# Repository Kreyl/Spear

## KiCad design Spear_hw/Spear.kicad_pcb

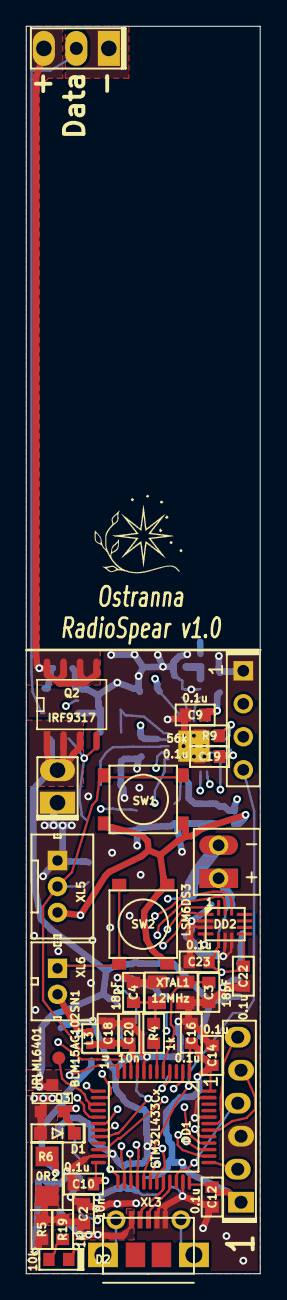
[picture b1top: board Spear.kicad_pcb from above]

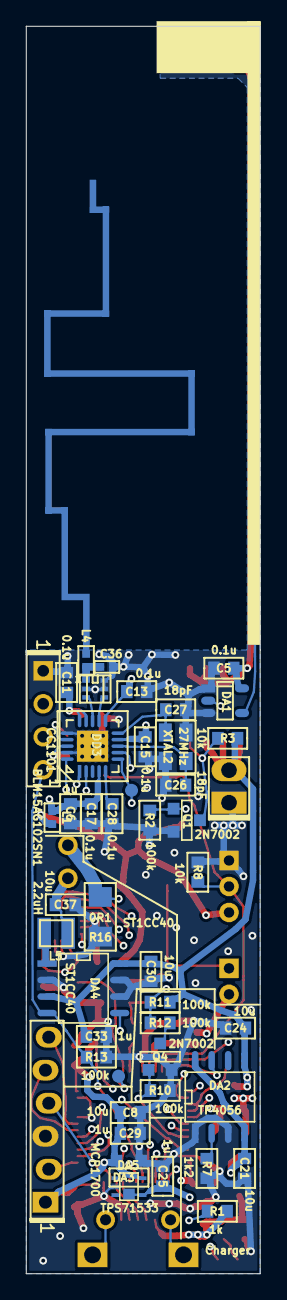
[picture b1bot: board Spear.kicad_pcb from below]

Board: 4 copper layers, 18.0 x 96.0 mm, 82 parts (44 on the bottom side), 58 nets.

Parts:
ANT1: ANT_PCB_MONO; ANT_868_Spear_inverted
BLN1: BALUN868JOHANSON; BALUN_JOHANSON868
C2, C20: 10n; CAP_0603_Silks
C3, C4, C26, C27: 18pF; CAP_0603_Silks
C5, C9, C10, C11, C12, C13, C14, C15, C16, C17, C19, C22, C23, C28: 0.1u; CAP_0603_Silks
C6, C18, C25, C29, C33: 1u; CAP_0603_Silks
C8, C21, C24, C30, C37: 10u; CAP_0603_Silks
C36: *; CAP_0402
D1: NSR0320; SOD323
D2: LED; LED_0603
DA1: MC74VHC1; SOT23-5
DA2: TP4056; SO8_150MIL
DA3: MCP1700; SOT23-3A
DA4: ST1CC40; SO8_150MIL
DA5: TPS71533; SOT323
DD1: STM32L433Cx; LQFP48
DD2: LSM6DS3; 14_3x2d5_p0d5
DD3: CC1101; QFN20
L1, L3: BLM15AG102SN1; IND_0402
L4: *; IND_0402
L5: 2.2uH; IND_SRN2512
Logo1: Logo; Ostranna_8x8
Q1, Q4: 2N7002; SOT23-3
Q2: IRF9317; SO8_150MIL
Q3: IRLML6401; SOT23-3
R1, R4, R19: 1k; RES_0603
R2, R10, R11, R12, R13: 100k; RES_0603
R3, R5, R8: 10k; RES_0603
R6: 0R2; RES_1206
R7: 1k2; RES_0603
R9: 56k; RES_0603
R16: 0R1; RES_1206
SW1, SW2: BUTTON; BTN_4x4_SMD
TP1, TP2, TP3: TESTPOINT; TESTPOINT_1MM
XL1: CONN_6; PLS-6_LOCK
XL2: CONN_2; SLD_2_2D5
XL3: USB_MICRO; USBmicro_MOLEX_1050170001
XL4: CONN_3; SLD_3_2D5
XL5: CONN_3; WB-03(MW-3M)
XL6: CONN_2; WB-02(MW-2M)
XL7: CONN_2; Oval3x1.5wHole0d9_x2
XL8: CONN_4; PLS-4
XTAL1: 12MHz; 03225C4
XTAL2: 27MHz; 03225C4

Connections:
+3v3: C8.2, C10.1, C12.1, C14.1, C16.1, C29.1, DA3.2, DA5.5, DD1.1, DD1.24, DD1.36, DD1.48, L1.2, L3.1, SW1.2, SW2.2, XL1.1, XL5.3, XL6.2
+BATT: C24.2, C30.1, C33.1, DA2.5, DA4.3, DA4.8, Q2.1, Q2.2, Q2.3, Q3.3, R3.1, R11.1, XL2.2
/5V_MID: C21.2, DA2.4, DA2.8, R6.2
/5V_USB: C2.2, D1.A, Q3.1, R1.2, R5.1, R6.1, R19.2, XL3.1
/ACC_CS: DD1.25, DD2.12
/ACC_INT1: DD1.2, DD2.4
/ACC_MISO: DD1.27, DD2.1
/ACC_MOSI: DD1.28, DD2.14
/ACC_PWR: C22.1, C23.1, DD1.22, DD2.5, DD2.8
/ACC_SCK: DD1.26, DD2.13
/ADC_BAT: DD1.19, R11.2, R12.1
/ADC_BAT_EN: DD1.20, Q4.1, R10.1
/BTN1: DD1.10, R8.1, SW1.1, XL5.2
/BTN2: DD1.11, SW2.1, XL6.1
/CC_CS: DD1.38, DD3.7
/CC_GDO0: DD1.18, DD3.6, TP2.1
/CC_MISO: DD1.40, DD3.2
/CC_MOSI: DD1.41, DD3.20
/CC_SCK: DD1.39, DD3.1
/DIN0: DA1.4, XL4.2
/IS_CHARGING: D2.C, DA2.7, DD1.12
/LED_CTRL1: DA4.4, DD1.29, R13.1, XL8.4
/LED_CTRL2: DD1.30, XL8.3
/LED_CTRL3: DD1.31, XL8.2
/MCU_VDDA: C18.1, C20.1, DD1.9, L3.2
/NPX1_CTRL: DA1.2, DD1.17
/NPX_PWR: C5.2, DA1.5, Q2.5, Q2.6, Q2.7, Q2.8, XL4.3
/NPX_PWR_EN: DD1.14, Q1.1, R2.2
/RF1: BLN1.4, DD3.12
/RF2: BLN1.3, DD3.13
/SWCLK: DD1.37, XL1.2
/SWDIO: DD1.34, XL1.4
/UART_RX: DD1.43, XL1.6
/UART_TX: DD1.42, XL1.5
/USB_DM: DD1.32, XL3.2
/USB_DP: DD1.33, XL3.3
GND: BLN1.2, BLN1.5, BLN1.6, C2.1, C3.2, C4.2, C5.1, C6.2, C8.1, C9.2, C10.2, C11.2, C12.2, C13.2, C14.2, C15.2, C16.2, C17.2, C18.2, C19.2, C20.2, C21.1, C22.2, C23.2, C24.1, C25.2, C26.2, C27.2, C28.1, C29.2, C30.2, C33.2, C36.2, C37.2, DA1.1, DA1.3, DA2.1, DA2.3, DA3.1, DA4.2, DA4.6, DA4.7, DA5.2, DD1.8, DD1.23, DD1.35, DD1.44, DD1.47, DD2.2, DD2.3, DD2.6, DD2.7, DD3.16, DD3.19, DD3.PAD, Q1.2, Q4.2, R2.1, R5.2, R7.2, R8.2, R9.2, R10.2, R13.2, R16.2, XL1.3, XL2.1, XL3.4, XL3.5, XL4.1, XL5.1, XL8.1, XTAL1.H, XTAL2.H
unnamed: ANT1.1, L4.2
unnamed: BLN1.1, C36.1, L4.1
unnamed: C3.1, DD1.5, XTAL1.1
unnamed: C4.1, R4.2, XTAL1.2
unnamed: C26.1, DD3.8, XTAL2.1
unnamed: C27.1, DD3.10, XTAL2.2
unnamed: C28.2, DD3.5
unnamed: C37.1, L5.1, XL7.1
unnamed: D2.A, R19.1
unnamed: DA2.2, R7.1
unnamed: DA4.1, L5.2
unnamed: DA4.5, R16.1, XL7.2
unnamed: DD1.4, TP1.1
unnamed: DD1.6, R4.1
unnamed: DD1.13, R1.1
unnamed: DD1.15, DD1.16, TP3.1
unnamed: DD3.17, R9.1
unnamed: Q1.3, Q2.4, R3.2
unnamed: Q4.3, R12.2
PwrUnst: C25.1, D1.C, DA3.3, DA5.4, Q3.2
VCC: C6.1, C9.1, C11.1, C13.1, C15.1, C17.1, C19.1, DD3.4, DD3.9, DD3.11, DD3.14, DD3.15, DD3.18, L1.1

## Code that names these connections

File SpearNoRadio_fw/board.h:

#pragma once

// ==== General ====
#define BOARD_NAME          "Spear01"
#define APP_NAME            "StaffWings"

#ifndef TRUE
#define TRUE    1
#endif

// ==== High-level peripery control ====
#define PILL_ENABLED        FALSE
#define BEEPER_ENABLED      FALSE
#define BUTTONS_ENABLED     TRUE

#define SIMPLESENSORS_ENABLED   BUTTONS_ENABLED

// MCU type as defined in the ST header.
#define STM32L151xB

// Freq of external crystal if any. Leave it here even if not used.
#define CRYSTAL_FREQ_HZ 12000000

// OS timer settings
#define STM32_ST_IRQ_PRIORITY   2
#define STM32_ST_USE_TIMER      2
#define SYS_TIM_CLK             (Clk.APB1FreqHz)

#define ADC_REQUIRED    TRUE

// LEDs config: BandCnt; {LedCnt1, LedCnt2, LedCnt3...}
#define FLAME_LEN       10
#define BAND_CNT        3
#define BAND_SETUPS     ((const BandSetup_t[]){\
    {FLAME_LEN, dirForward}, \
    {FLAME_LEN, dirBackward}, \
    {FLAME_LEN, dirForward}, \
    })

#if 1 // ========================== GPIO =======================================
// PortMinTim_t: GPIO, Pin, Tim, TimChnl, invInverted, omPushPull, TopValue
// UART
#define UART_GPIO       GPIOA
#define UART_TX_PIN     9
#define UART_RX_PIN     10

// Buttons
#define BTN1_PIN        GPIOA, 0
#define BTN2_PIN        GPIOA, 1

// Charging
#define IS_CHARGING_PIN GPIOA, 2, pudPullUp

// Npx LEDs
#define NPX_SPI         SPI1
#define NPX_DATA_PIN    GPIOA, 7, AF5
#define NPX_PWR_PIN     GPIOA, 6

// ADC
#define ADC_BAT_EN      GPIOB, 2
#define ADC_BAT_PIN     GPIOB, 1

#endif // GPIO

#if ADC_REQUIRED // ======================= Inner ADC ==========================
// Clock divider: clock is generated from the APB2
#define ADC_CLK_DIVIDER     adcDiv2

#define BAT_CHNL            9
#define ADC_VREFINT_CHNL    17  // All 4xx, F072 and L151 devices. Do not change.
#define ADC_CHANNELS        { BAT_CHNL, ADC_VREFINT_CHNL }
#define ADC_CHANNEL_CNT     2   // Do not use countof(AdcChannels) as preprocessor does not know what is countof => cannot check
#define ADC_SAMPLE_TIME     ast96Cycles
#define ADC_SAMPLE_CNT      8   // How many times to measure every channel
#define ADC_SEQ_LEN         (ADC_SAMPLE_CNT * ADC_CHANNEL_CNT)
#endif

#if 1 // =========================== DMA =======================================
#define STM32_DMA_REQUIRED  TRUE
// ==== Uart ====
#define UART_DMA_TX_MODE(Chnl) (STM32_DMA_CR_CHSEL(Chnl) | DMA_PRIORITY_LOW | STM32_DMA_CR_MSIZE_BYTE | STM32_DMA_CR_PSIZE_BYTE | STM32_DMA_CR_MINC | STM32_DMA_CR_DIR_M2P | STM32_DMA_CR_TCIE)
#define UART_DMA_RX_MODE(Chnl) (STM32_DMA_CR_CHSEL(Chnl) | DMA_PRIORITY_MEDIUM | STM32_DMA_CR_MSIZE_BYTE | STM32_DMA_CR_PSIZE_BYTE | STM32_DMA_CR_MINC | STM32_DMA_CR_DIR_P2M | STM32_DMA_CR_CIRC)
#define UART_DMA_TX     STM32_DMA_STREAM_ID(1, 4)
#define UART_DMA_RX     STM32_DMA_STREAM_ID(1, 5)
#define UART_DMA_CHNL   0   // Dummy

// ==== Npx ====
#define NPX_DMA         STM32_DMA_STREAM_ID(1, 3)  // SPI1 TX

#if ADC_REQUIRED
#define ADC_DMA         STM32_DMA_STREAM_ID(1, 1)
#define ADC_DMA_MODE    STM32_DMA_CR_CHSEL(0) |   /* dummy */ \
                        DMA_PRIORITY_LOW | \
                        STM32_DMA_CR_MSIZE_HWORD | \
                        STM32_DMA_CR_PSIZE_HWORD | \
                        STM32_DMA_CR_MINC |       /* Memory pointer increase */ \
                        STM32_DMA_CR_DIR_P2M |    /* Direction is peripheral to memory */ \
                        STM32_DMA_CR_TCIE         /* Enable Transmission Complete IRQ */
#endif // ADC

#endif // DMA

#if 1 // ========================== USART ======================================
#define PRINTF_FLOAT_EN FALSE
#define UART_TXBUF_SZ   256
#define UART_RXBUF_SZ   99

#define UARTS_CNT       1

#define CMD_UART_PARAMS \
    USART1, UART_GPIO, UART_TX_PIN, UART_GPIO, UART_RX_PIN, \
    UART_DMA_TX, UART_DMA_RX, UART_DMA_TX_MODE(UART_DMA_CHNL), UART_DMA_RX_MODE(UART_DMA_CHNL)

#endif

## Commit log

2019-11-12 Working on Antenna
2019-11-16 Tracing done, antenna not
2019-11-17 + Spear NoRadio sent to factory
2019-11-23 Move files, no changes
2019-12-03 + Compiled, UART and btn work
2019-12-04 + 10MHz out of HSI
2019-12-04 + Leds work
2019-12-05 + Moving flash
2019-12-06 + Sleep works
2019-12-07 + FadeIn-FadeOut
2019-12-07 + ADC + Sleep if battery discharged
2019-12-07 + Eff params tuned
2019-12-07 * Switch to os v 19.1.3
2019-12-09 + IsCharging
2019-12-14 + L151
2019-12-14 +L151-2
2019-12-14 Different band setups allowed
2019-12-14 Release
2019-12-21 + NextTime.txt
2020-03-21 + RadioSpear HW
2020-04-25 * Switch to CubeIDE
2022-03-18 Something
2022-06-13 Testing LEDs count in every piece: snake head, snake tail, and the moon
2022-06-15 Fade-in
2023-01-26 Nothing
2023-01-26 Switch to CubeIDE
2023-02-15 App name changed
2023-02-15 Maybe, it will work
2024-02-04 Switching to Eclipse
2024-02-04 Compiled
2024-02-16 LEDs work
2024-07-04 Refactoring
2024-07-06 Flame works
2024-07-06 Tinwi seem good
2024-07-06 Fighting with fadein-fadeout
2024-07-06 FadeIn/FadeOut fixed
2024-07-07 + hex
